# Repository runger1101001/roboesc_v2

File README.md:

# roboesc_v2

Very tiny breakout board for the STM233. Feel free to use the design in any way you would like. Design files are in KiCad 5. Gerbers are in the v1/ directory.

Personally, I would not recommend fabricating it as is. It is too small, making it a bit inconvenient to use.

Front:

Back:

Fabricated result, next to a Bluepill board for size comparison:

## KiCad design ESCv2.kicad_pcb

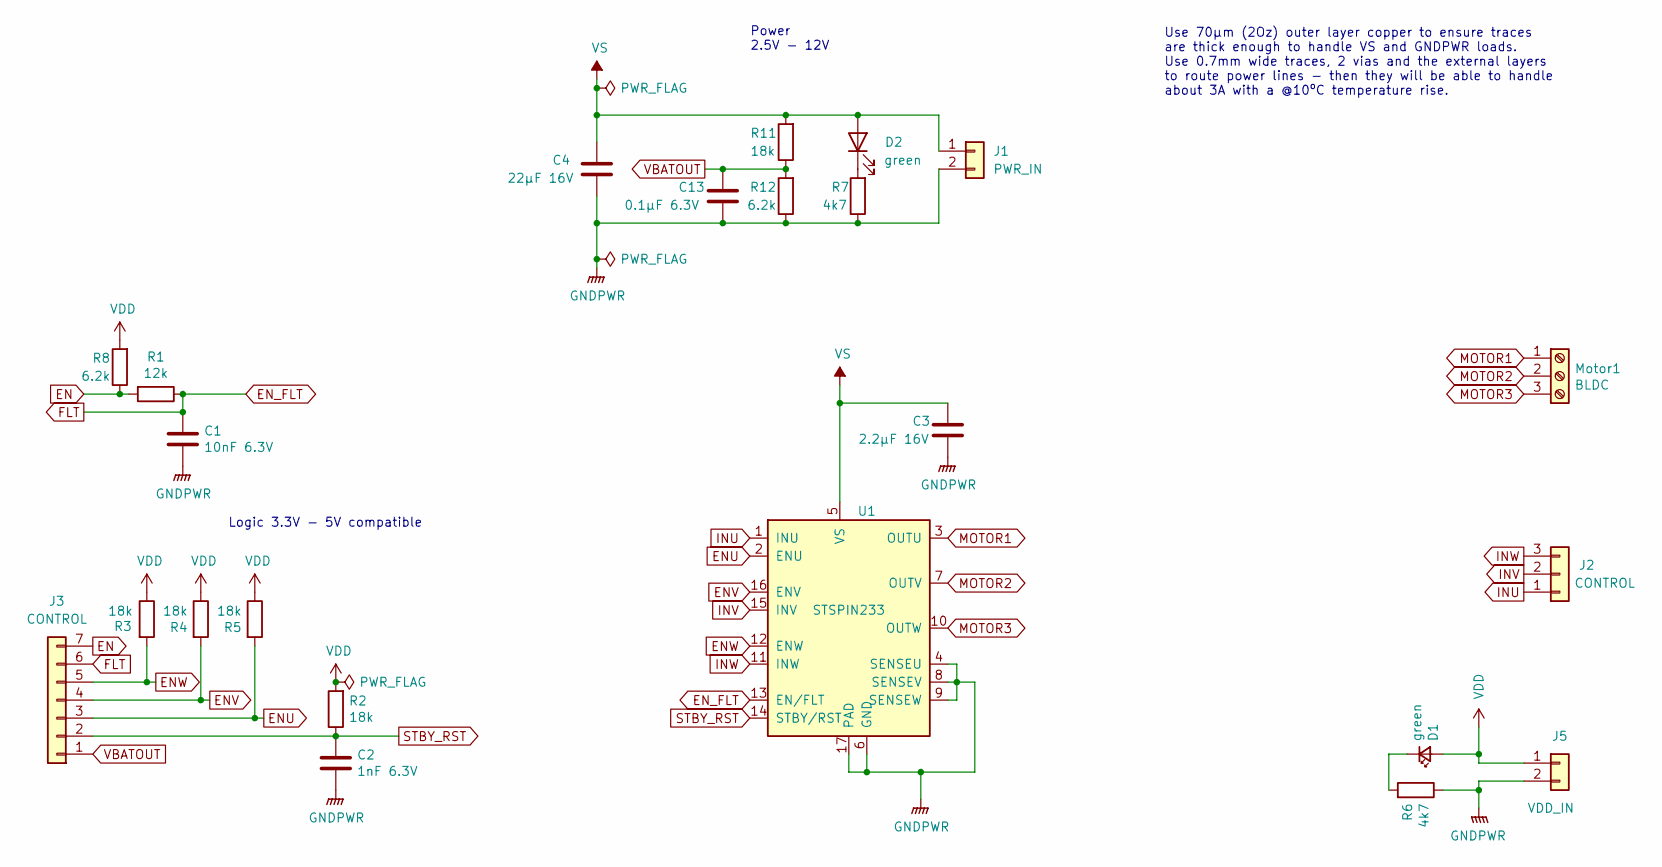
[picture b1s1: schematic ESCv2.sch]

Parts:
C1: 10nF 6.3V; C_0402_1005Metric
C2: 1nF 6.3V; C_0402_1005Metric
C3: 2.2μF 16V; C_0805_2012Metric
C4: 22μF 16V; C_1206_3216Metric
C13: 0.1µF 6.3V; C_0402_1005Metric
D1, D2: green; LED_0402_1005Metric
J1: PWR_IN; PinHeader_1x02_P2.54mm_Vertical
J2: CONTROL; PinHeader_1x03_P2.54mm_Vertical
J3: CONTROL; PinHeader_1x07_P1.27mm_Vertical
J5: VDD_IN; PinHeader_1x02_P2.54mm_Vertical
Motor1: BLDC; PinHeader_1x03_P2.54mm_Vertical
R1: 12k; R_0402_1005Metric
R2, R3, R4, R5, R11: 18k; R_0402_1005Metric
R6, R7: 4k7; R_0402_1005Metric
R8, R12: 6.2k; R_0402_1005Metric
U1: STSPIN233; VQFN-16-1EP_3x3mm_P0.5mm_EP1.8x1.8mm

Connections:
EN: J3.7, R1.2, R8.1
ENU: J3.3, R5.2, U1.2 (ENU)
ENV: J3.4, R4.2, U1.16 (ENV)
ENW: J3.5, R3.2, U1.12 (ENW)
EN_FLT: C1.1, J3.6, R1.1, U1.13 (EN/FLT)
GNDPWR: C1.2, C2.2, C3.2, C4.2, C13.2, J1.2, J5.2, R6.1, R7.1, R12.1, U1.4 (SENSEU), U1.6 (GND), U1.8 (SENSEV), U1.9 (SENSEW), U1.17 (PAD)
INU: J2.1, U1.1 (INU)
INV: J2.2, U1.15 (INV)
INW: J2.3, U1.11 (INW)
MOTOR1: Motor1.1, U1.3 (OUTU)
MOTOR2: Motor1.2, U1.7 (OUTV)
MOTOR3: Motor1.3, U1.10 (OUTW)
unnamed: D1.1 (K), R6.2
unnamed: D2.1 (K), R7.2
STBY_RST: C2.1, J3.2, R2.1, U1.14 (STBY/RST)
VBATOUT: C13.1, J3.1, R11.1, R12.2
VDD: D1.2 (A), J5.1, R2.2, R3.1, R4.1, R5.1, R8.2
VS: C3.1, C4.1, D2.2 (A), J1.1, R11.2, U1.5 (VS)

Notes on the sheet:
Logic 3.3V - 5V compatible
Power 2.5V - 12V
Use 70µm (2Oz) outer layer copper to ensure traces are thick enough to handle VS and GNDPWR loads. Use 0.7mm wide traces, 2 vias and the external layers to route power lines - then they will be able to handle about 3A with a @10ºC temperature rise.

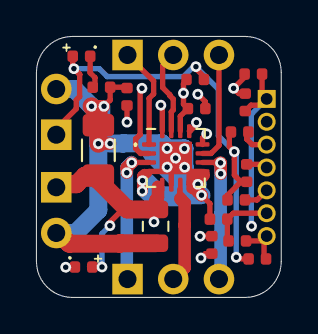
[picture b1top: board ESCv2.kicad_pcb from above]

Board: 4 copper layers, 13.6 x 14.5 mm, 23 parts (0 on the bottom side), 18 nets.

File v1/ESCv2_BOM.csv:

Item #,Ref Des,Qty,Manufacturer,Mfg Part #, Description / Value,Package,Type,Your Instructions / Notes
1,"D1,D2",2,Generic,Generic,LED Green (? 560nm)  Vf 2.1V @20mA,0402 (LED),SMD,"Generic, e.g. https://eu.mouser.com/datasheet/2/348/sml-p1-e-1874493.pdf"
2,U1,1,ST Micro,STSPIN233,STSPIN233,VQFN-16-1EP_3x3mm_P0.5mm_EP1.8x1.8mm,SMD,https://www.st.com/en/motor-drivers/stspin233.html#overview
3,"R12,R8",2,Generic,Generic,6.2k,0402,SMD,Generic
4,"R11,R5,R4,R3,R2",5,Generic,Generic,18k,0402,SMD,Generic
5,"R7,R6",2,Generic,Generic,4k7,0402,SMD,Generic
6,R1,1,Generic,Generic,12k,0402,SMD,Generic
7,C13,1,Generic,Generic,0.1µF 6.3V,0402,SMD,Generic
8,C4,1,Generic,Generic,22?F 16V,1206,SMD,Generic
9,C3,1,Generic,Generic,2.2?F 16V,0805,SMD,Generic
10,C2,1,Generic,Generic,1nF 6.3V,0402,SMD,Generic
11,C1,1,Generic,Generic,10nF 6.3V,0402,SMD,Generic

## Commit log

2021-05-05 first import
2021-05-05 Some pics
2021-05-06 missing files
